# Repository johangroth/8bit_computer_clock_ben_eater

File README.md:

# 8bit_computer_clock_ben_eater

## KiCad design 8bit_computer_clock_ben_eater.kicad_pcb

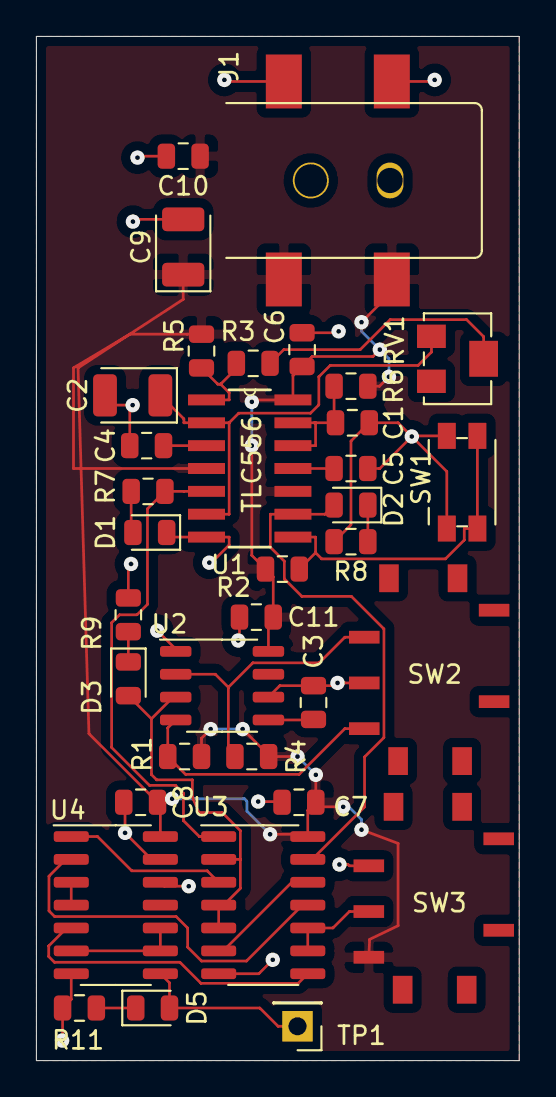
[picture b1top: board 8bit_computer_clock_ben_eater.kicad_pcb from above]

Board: 2 copper layers, 26.8 x 56.9 mm, 35 parts (0 on the bottom side), 27 nets.

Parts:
C1, C10: 100nF; C_0805_2012Metric
C2: 1uF; CP_EIA-3528-12_Kemet-T
C3, C4, C5: 10nF; C_0805_2012Metric
C6, C7, C8, C11: 0.1uF; C_0805_2012Metric
C9: 100uF; CP_EIA-3528-12_Kemet-T
D1, D2, D3, D5: LED; LED_0805_2012Metric
J1: Barrel_Jack_Switch; Barrel Jack RS Pro DC Socket 2.5mm - SMT
R1, R2, R3, R4, R5: 1k; R_0805_2012Metric
R6: 1M; R_0805_2012Metric
R7, R8, R9, R11: 220; R_0805_2012Metric
RV1: 1M; Potentiometer_Bourns_3214W_Vertical
SW1: Step; Panasonic_EVQPUK_EVQPUB
SW2: Switch; G3T12
SW3: Halt; G3T12
TP1: CLK; PinHeader_1x01_P2.54mm_Vertical
U1: TLC556; SOIC127P600X175-14N
U2: LMC555xN; SO-8_3.9x4.9mm_P1.27mm
U3, U4: 74HC00; SOIC-14_3.9x8.7mm_P1.27mm

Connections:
/CONTA: C4.2, U1.3
/CONTB: C5.2, U1.11
/CV: C3.1, U2.5
/DISCHA: R3.1, R5.2, U1.1
/OUTA: R7.2, U1.5, U3.1
/OUTB: D2.2, U1.9, U3.13
/Q: D3.2, U2.3, U3.2, U3.4, U3.5
/R: R1.2, SW2.3, U2.4
/THRESB: C1.2, R6.1, U1.12, U1.13
/THRESHA: C2.1, RV1.1, U1.2, U1.6
/TR: R4.2, SW2.1, U2.2
/TRIGB: R2.2, SW1.2, U1.8
GND: C1.1, C2.2, C3.2, C4.1, C5.1, C6.2, C7.2, C8.2, C9.2, C10.2, C11.2, D1.1, J1.2, J1.3, R8.2, R9.1, R11.2, SW1.1, SW2.2, SW3.1, U1.7, U2.1, U2.6, U3.7, U4.7, U4.12, U4.13
unnamed: D1.2, R7.1
unnamed: D2.1, R8.1
unnamed: D3.1, R9.2
unnamed: D5.1, R11.1
unnamed: D5.2, TP1.1, U4.8
unnamed: R3.2, RV1.2
unnamed: SW3.2, U3.9, U3.10
unnamed: U3.3, U4.1
unnamed: U3.8, U4.5
unnamed: U3.11, U4.2
unnamed: U3.6, U3.12
unnamed: U4.3, U4.4
unnamed: U4.6, U4.9, U4.10
VCC: C6.1, C7.1, C8.1, C9.1, C10.1, C11.1, J1.1, R1.1, R2.1, R4.1, R5.1, R6.2, SW3.3, U1.4, U1.10, U1.14, U2.8, U3.14, U4.14

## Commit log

2019-09-28 Initial commit.
2019-09-28 New pcb layout. Added power connection.
2019-10-30 Changed all footprints to SMD/SMT. Used a 556 instead of two 555. Beginning of a PCB.
2019-11-07 PCB finished.
2019-11-07 Fixed traces autorouter failed to route. Ordered PCB with OSHPark.
